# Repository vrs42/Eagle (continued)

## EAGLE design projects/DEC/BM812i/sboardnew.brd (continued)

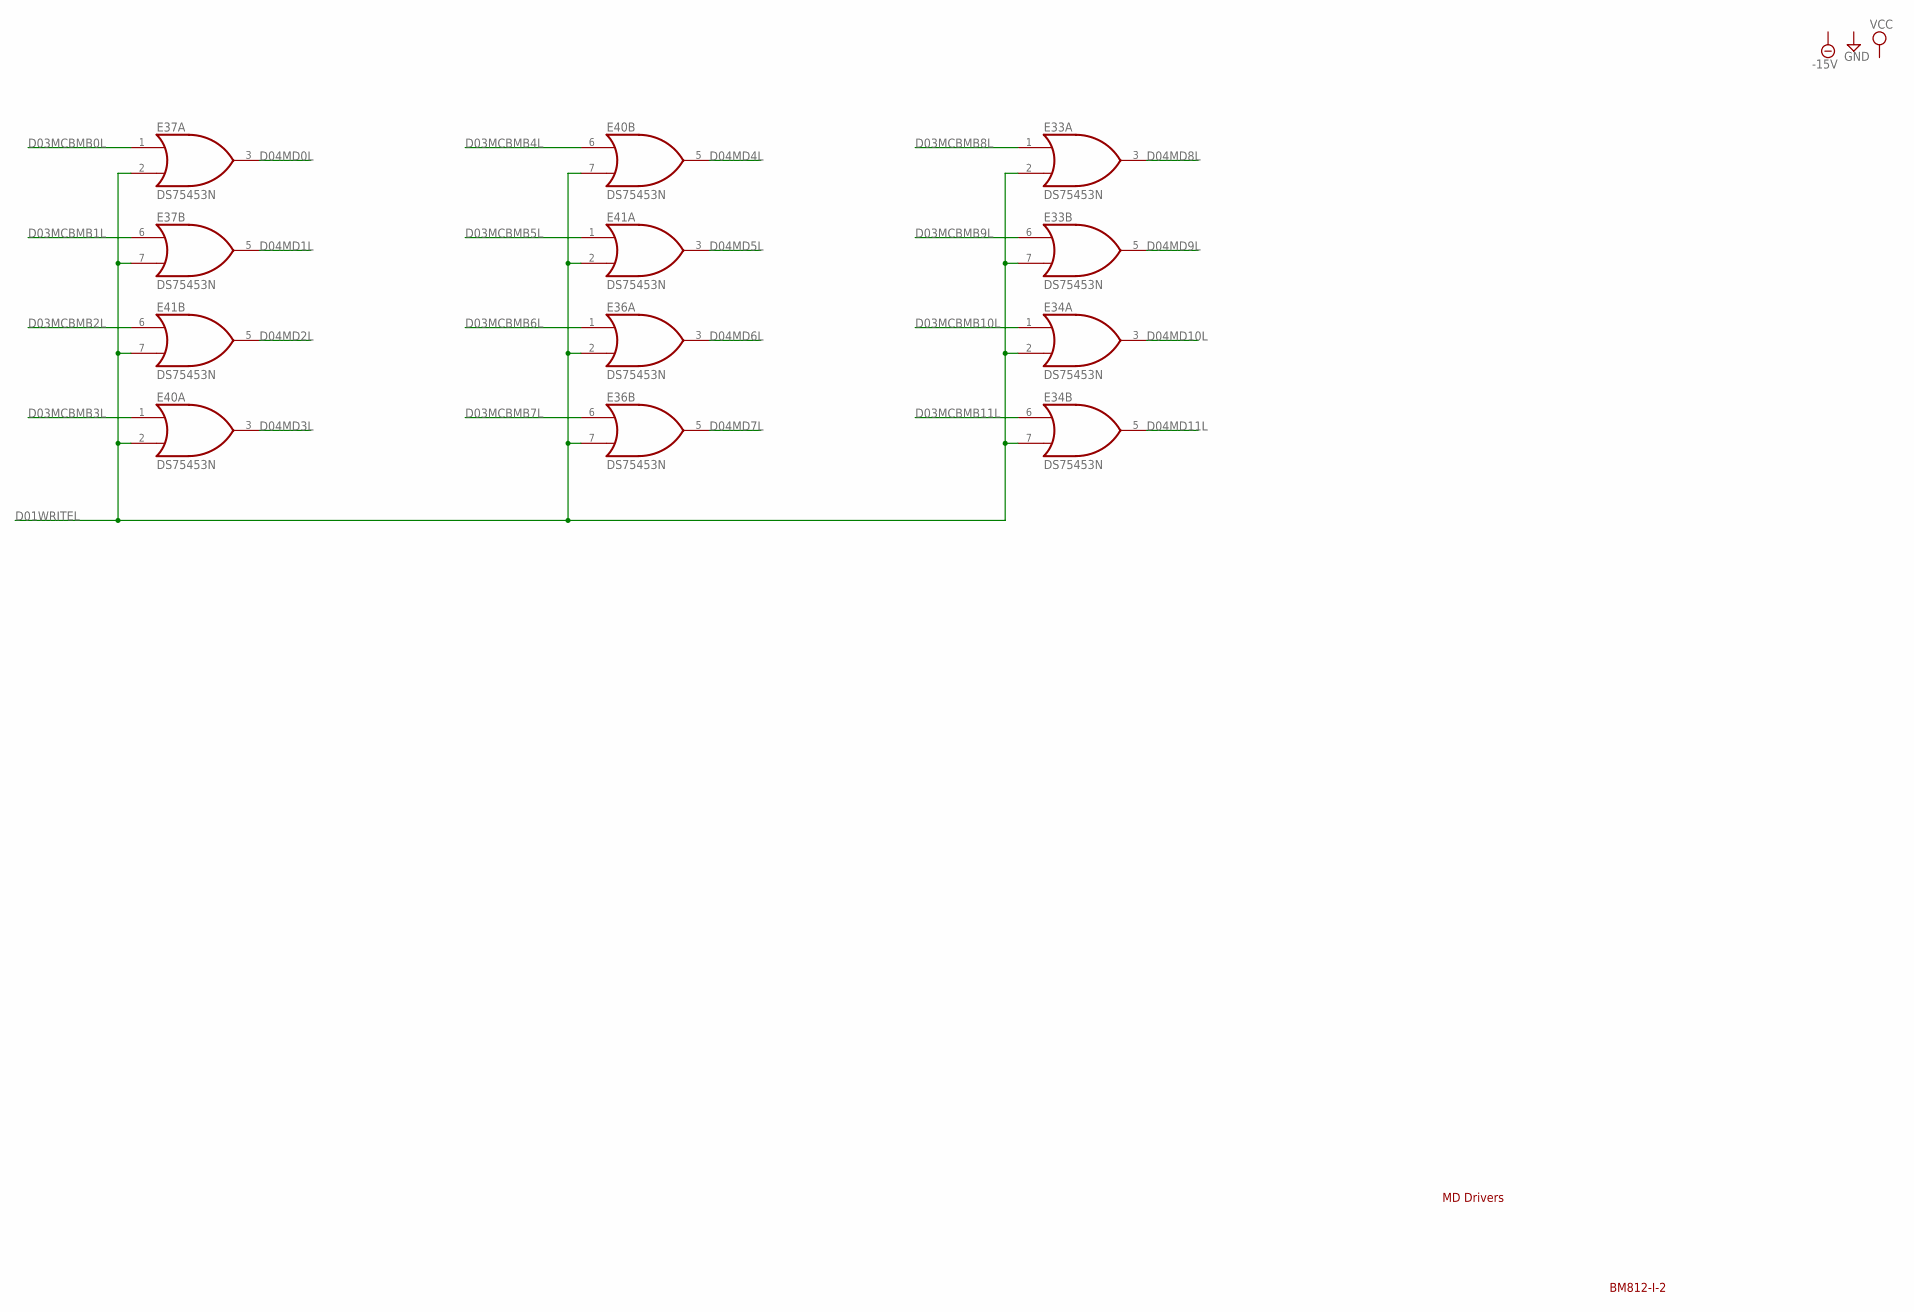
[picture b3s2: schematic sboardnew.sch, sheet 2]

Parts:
E33, E34, E36, E37, E40, E41: DS75453N; DIL08

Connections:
D01WRITEL: E33.2 (I1), E33.7 (I1), E34.2 (I1), E34.7 (I1), E36.2 (I1), E36.7 (I1), E37.2 (I1), E37.7 (I1), E40.2 (I1), E40.7 (I1), E41.2 (I1), E41.7 (I1); also elsewhere on the board
D03MCBMB0L: E37.1 (I0); also elsewhere on the board
D03MCBMB1L: E37.6 (I0); also elsewhere on the board
D03MCBMB2L: E41.6 (I0); also elsewhere on the board
D03MCBMB3L: E40.1 (I0); also elsewhere on the board
D03MCBMB4L: E40.6 (I0); also elsewhere on the board
D03MCBMB5L: E41.1 (I0); also elsewhere on the board
D03MCBMB6L: E36.1 (I0); also elsewhere on the board
D03MCBMB7L: E36.6 (I0); also elsewhere on the board
D03MCBMB8L: E33.1 (I0); also elsewhere on the board
D03MCBMB9L: E33.6 (I0); also elsewhere on the board
D03MCBMB10L: E34.1 (I0); also elsewhere on the board
D03MCBMB11L: E34.6 (I0); also elsewhere on the board
D04MD0L: E37.3 (O); also elsewhere on the board
D04MD1L: E37.5 (O); also elsewhere on the board
D04MD2L: E41.5 (O); also elsewhere on the board
D04MD3L: E40.3 (O); also elsewhere on the board
D04MD4L: E40.5 (O); also elsewhere on the board
D04MD5L: E41.3 (O); also elsewhere on the board
D04MD6L: E36.3 (O); also elsewhere on the board
D04MD7L: E36.5 (O); also elsewhere on the board
D04MD8L: E33.3 (O); also elsewhere on the board
D04MD9L: E33.5 (O); also elsewhere on the board
D04MD10L: E34.3 (O); also elsewhere on the board
D04MD11L: E34.5 (O); also elsewhere on the board
GND: E33.4 (GND), E34.4 (GND), E36.4 (GND), E37.4 (GND), E40.4 (GND), E41.4 (GND); also elsewhere on the board
VCC: E33.8 (VCC), E34.8 (VCC), E36.8 (VCC), E37.8 (VCC), E40.8 (VCC), E41.8 (VCC); also elsewhere on the board

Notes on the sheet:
BM812-I-2
MD Drivers

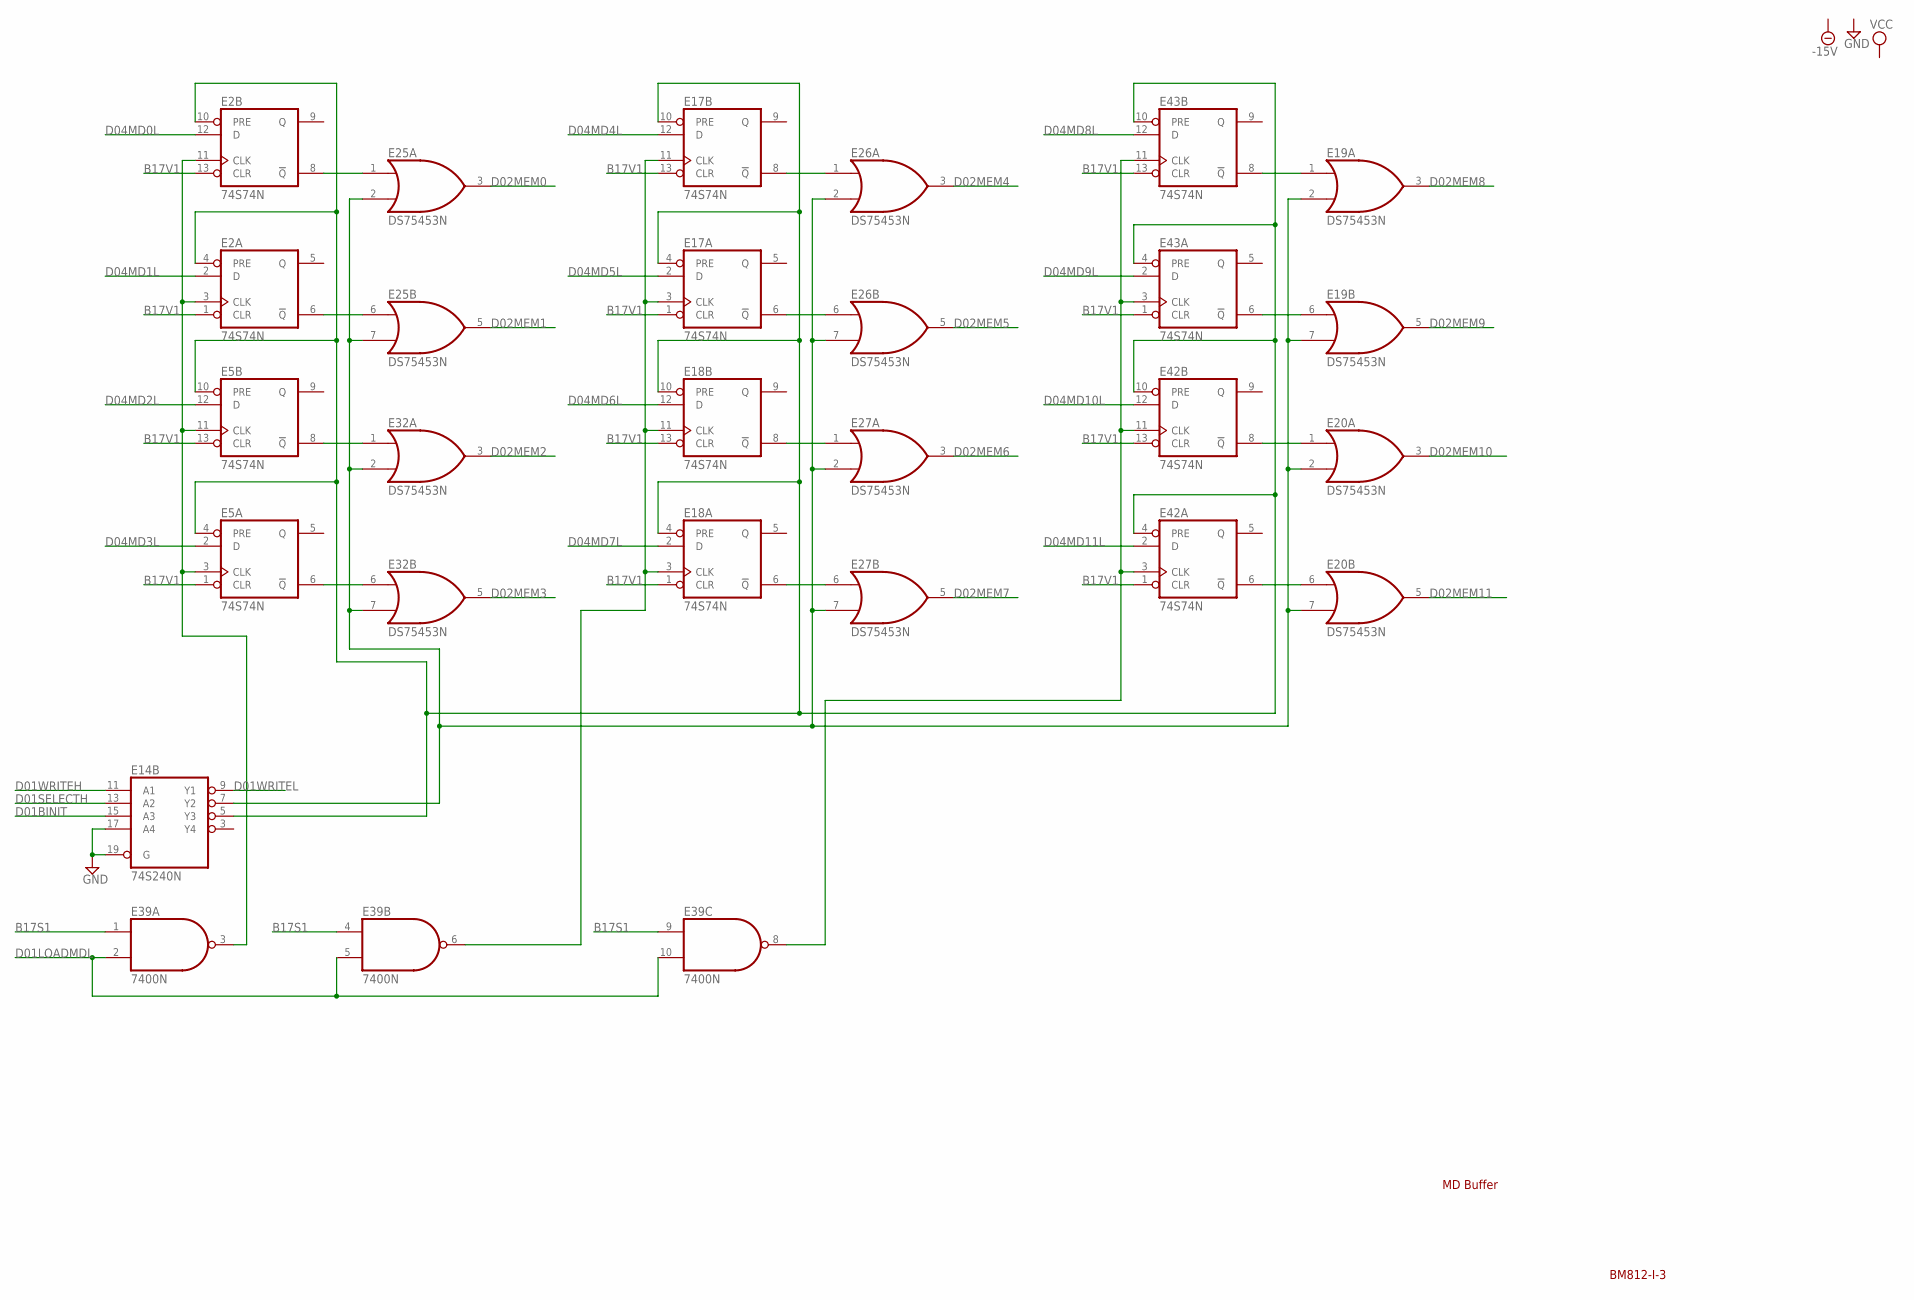
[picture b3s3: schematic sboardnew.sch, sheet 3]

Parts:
E2, E5, E17, E18, E42, E43: 74S74N; DIL14
E14: 74S240N; DIL20
E19, E20, E25, E26, E27, E32: DS75453N; DIL08
E39: 7400N; DIL14

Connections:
B17S1: E39.1 (I0), E39.4 (I0), E39.9 (I0); also elsewhere on the board
B17V1: E2.1 (CLR), E2.13 (CLR), E5.1 (CLR), E5.13 (CLR), E17.1 (CLR), E17.13 (CLR), E18.1 (CLR), E18.13 (CLR), E42.1 (CLR), E42.13 (CLR), E43.1 (CLR), E43.13 (CLR); also elsewhere on the board
D01BINIT: E14.15 (A3); also elsewhere on the board
D01LOADMDL: E39.2 (I1), E39.5 (I1), E39.10 (I1); also elsewhere on the board
D01SELECTH: E14.13 (A2); also elsewhere on the board
D01WRITEH: E14.11 (A1); also elsewhere on the board
D01WRITEL: E14.9 (Y1); also elsewhere on the board
D02MEM0: E25.3 (O); also elsewhere on the board
D02MEM1: E25.5 (O); also elsewhere on the board
D02MEM2: E32.3 (O); also elsewhere on the board
D02MEM3: E32.5 (O); also elsewhere on the board
D02MEM4: E26.3 (O); also elsewhere on the board
D02MEM5: E26.5 (O); also elsewhere on the board
D02MEM6: E27.3 (O); also elsewhere on the board
D02MEM7: E27.5 (O); also elsewhere on the board
D02MEM8: E19.3 (O); also elsewhere on the board
D02MEM9: E19.5 (O); also elsewhere on the board
D02MEM10: E20.3 (O); also elsewhere on the board
D02MEM11: E20.5 (O); also elsewhere on the board
D04MD0L: E2.12 (D); also elsewhere on the board
D04MD1L: E2.2 (D); also elsewhere on the board
D04MD2L: E5.12 (D); also elsewhere on the board
D04MD3L: E5.2 (D); also elsewhere on the board
D04MD4L: E17.12 (D); also elsewhere on the board
D04MD5L: E17.2 (D); also elsewhere on the board
D04MD6L: E18.12 (D); also elsewhere on the board
D04MD7L: E18.2 (D); also elsewhere on the board
D04MD8L: E43.12 (D); also elsewhere on the board
D04MD9L: E43.2 (D); also elsewhere on the board
D04MD10L: E42.12 (D); also elsewhere on the board
D04MD11L: E42.2 (D); also elsewhere on the board
GND: E2.7 (GND), E5.7 (GND), E14.10 (GND), E14.17 (A4), E14.19 (G), E17.7 (GND), E18.7 (GND), E19.4 (GND), E20.4 (GND), E25.4 (GND), E26.4 (GND), E27.4 (GND), E32.4 (GND), E39.7 (GND), E42.7 (GND), E43.7 (GND); also elsewhere on the board
unnamed: E2.3 (CLK), E2.11 (CLK), E5.3 (CLK), E5.11 (CLK), E39.3 (O)
unnamed: E5.6 (!Q), E32.6 (I0)
unnamed: E2.8 (!Q), E25.1 (I0)
unnamed: E2.6 (!Q), E25.6 (I0)
unnamed: E17.3 (CLK), E17.11 (CLK), E18.3 (CLK), E18.11 (CLK), E39.6 (O)
unnamed: E5.8 (!Q), E32.1 (I0)
unnamed: E2.4 (PRE), E2.10 (PRE), E5.4 (PRE), E5.10 (PRE), E14.5 (Y3), E17.4 (PRE), E17.10 (PRE), E18.4 (PRE), E18.10 (PRE), E42.4 (PRE), E42.10 (PRE), E43.4 (PRE), E43.10 (PRE)
unnamed: E14.7 (Y2), E19.2 (I1), E19.7 (I1), E20.2 (I1), E20.7 (I1), E25.2 (I1), E25.7 (I1), E26.2 (I1), E26.7 (I1), E27.2 (I1), E27.7 (I1), E32.2 (I1), E32.7 (I1)
unnamed: E17.6 (!Q), E26.6 (I0)
unnamed: E18.6 (!Q), E27.6 (I0)
unnamed: E18.8 (!Q), E27.1 (I0)
unnamed: E17.8 (!Q), E26.1 (I0)
unnamed: E20.6 (I0), E42.6 (!Q)
unnamed: E20.1 (I0), E42.8 (!Q)
unnamed: E39.8 (O), E42.3 (CLK), E42.11 (CLK), E43.3 (CLK), E43.11 (CLK)
unnamed: E19.6 (I0), E43.6 (!Q)
unnamed: E19.1 (I0), E43.8 (!Q)
VCC: E2.14 (VCC), E5.14 (VCC), E14.20 (VCC), E17.14 (VCC), E18.14 (VCC), E19.8 (VCC), E20.8 (VCC), E25.8 (VCC), E26.8 (VCC), E27.8 (VCC), E32.8 (VCC), E39.14 (VCC), E42.14 (VCC), E43.14 (VCC); also elsewhere on the board

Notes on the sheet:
MD Buffer
BM812-I-3

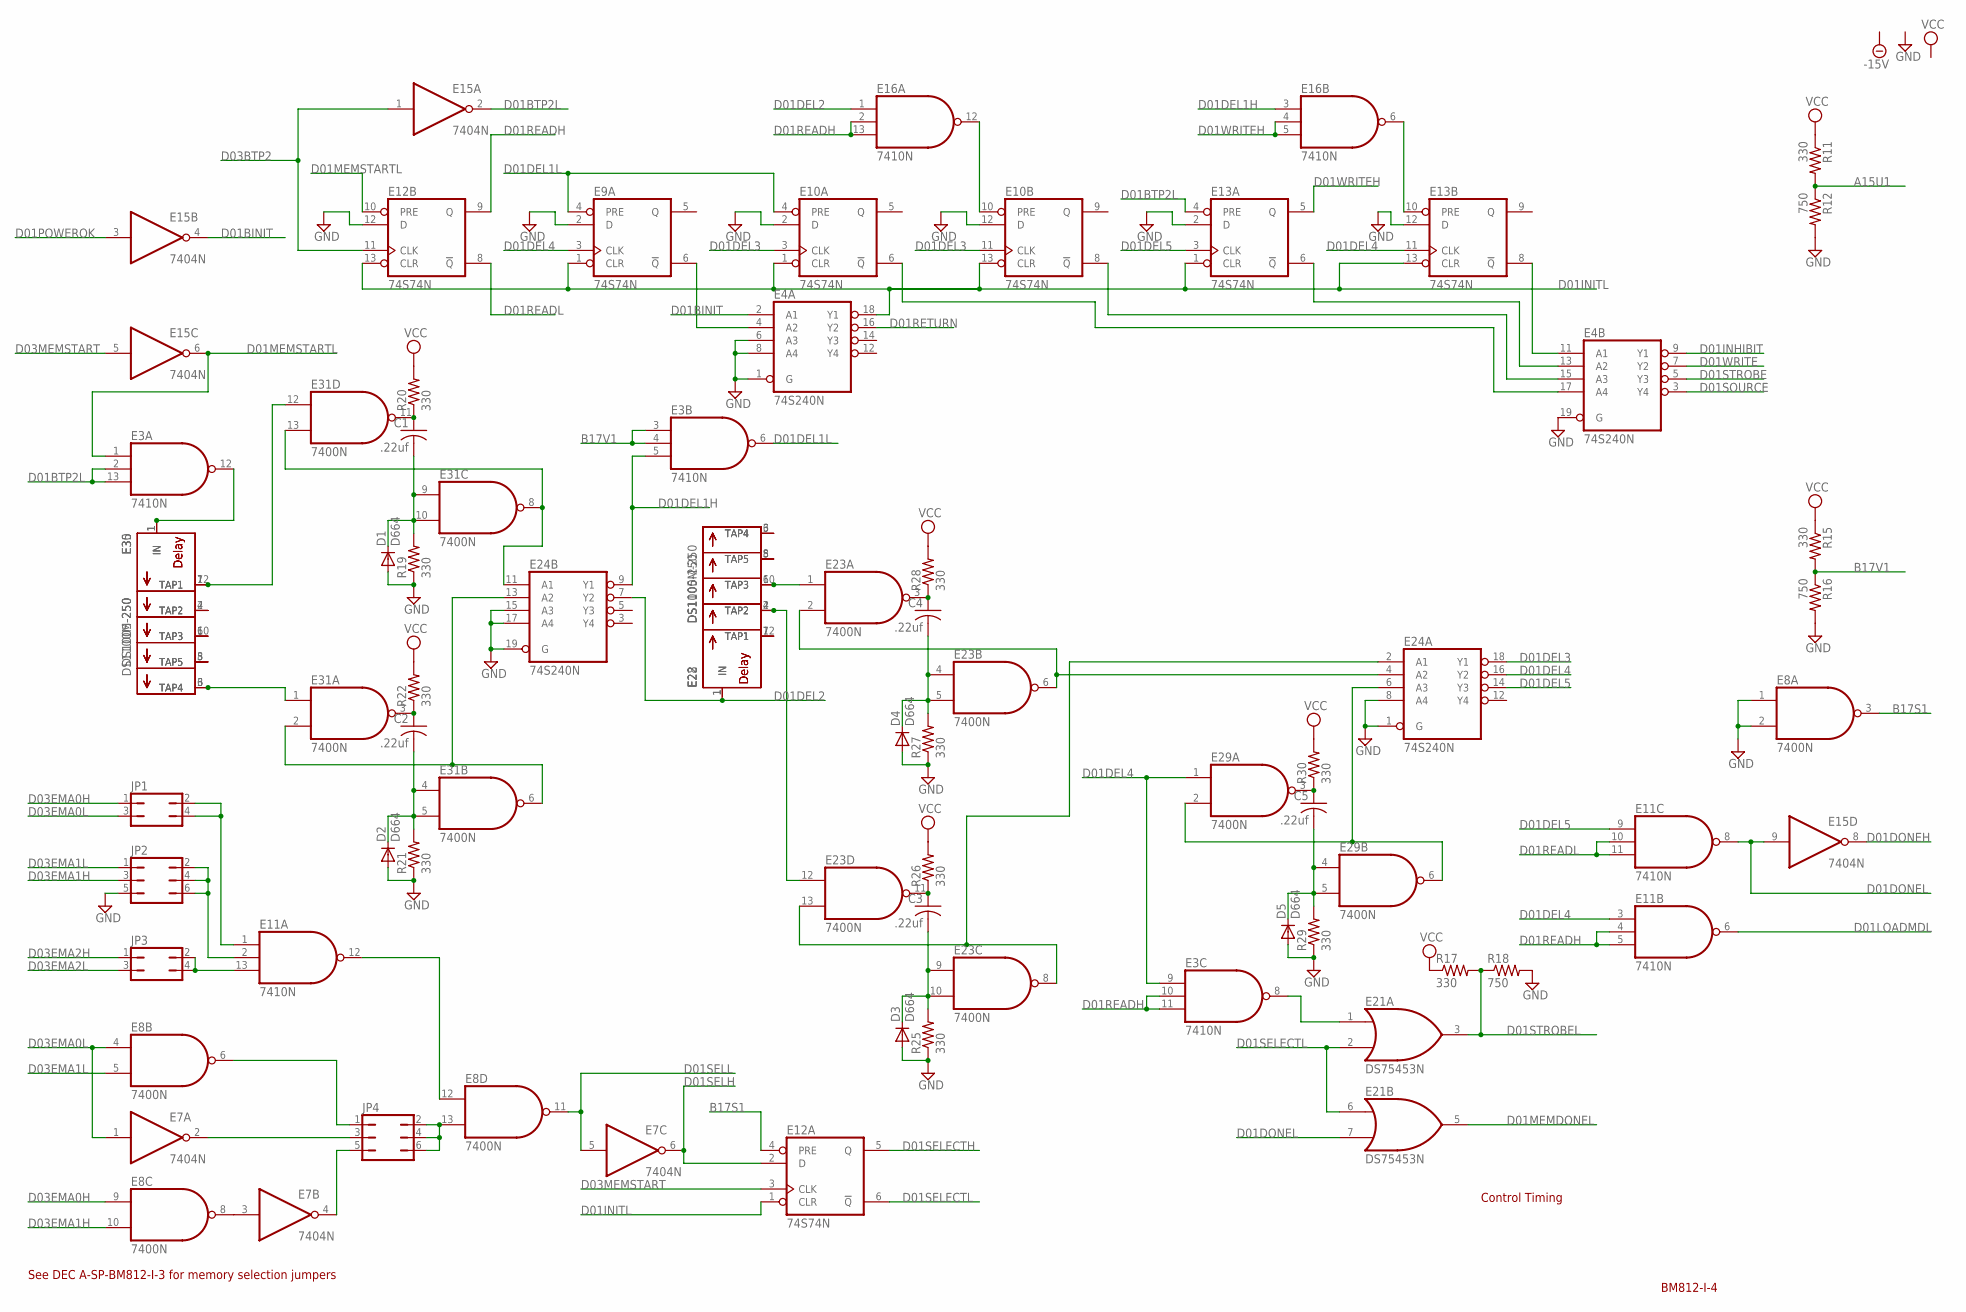
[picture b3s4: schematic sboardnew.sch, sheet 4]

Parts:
C1, C2, C3, C4, C5: .22uf; C050-025X075
D1, D2, D3, D4, D5: D664; DO35-10
E3, E11, E16: 7410N; DIL14
E4, E24: 74S240N; DIL20
E7, E15: 7404N; DIL14
E8, E23, E29, E31: 7400N; DIL14
E9, E10, E12, E13: 74S74N; DIL14
E21: DS75453N; DIL08
E22, E35: DS1100M-250; DIL08
E28, E30: DS1005-250; DIL14
JP1, JP3: JP2Q
JP2, JP4: JP3Q
R11, R15, R17, R19, R20, R21, R22, R25, R26, R27, R28, R29, R30: 330; 0207/10
R12, R16, R18: 750; 0207/10

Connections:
A15U1: R11.2, R12.1; also elsewhere on the board
B17S1: E8.3 (O), E12.4 (PRE); also elsewhere on the board
B17V1: E3.3 (I0), E3.4 (I1), R15.2, R16.1; also elsewhere on the board
D01BINIT: E4.2 (A1), E15.4 (O); also elsewhere on the board
D01BTP2L: E3.2 (I1), E3.13 (I2), E13.4 (PRE), E15.2 (O)
D01DEL1H: E3.5 (I2), E16.3 (I0), E24.9 (Y1)
D01DEL1L: E3.6 (O), E9.4 (PRE), E10.4 (PRE)
D01DEL2: E16.1 (I0), E22.1 (IN), E24.7 (Y2), E28.1 (IN)
D01DEL3: E10.3 (CLK), E10.11 (CLK), E24.18 (Y1)
D01DEL4: E3.9 (I0), E9.3 (CLK), E11.3 (I0), E13.11 (CLK), E24.16 (Y2), E29.1 (I0)
D01DEL5: E11.9 (I0), E13.3 (CLK), E24.14 (Y3)
D01DONEH: E15.8 (O); also elsewhere on the board
D01DONEL: E11.8 (O), E15.9 (I), E21.7 (I1)
D01INHIBIT: E4.9 (Y1); also elsewhere on the board
D01INITL: E4.18 (Y1), E9.1 (CLR), E10.1 (CLR), E10.13 (CLR), E12.1 (CLR), E12.13 (CLR), E13.1 (CLR), E13.13 (CLR)
D01LOADMDL: E11.6 (O); also elsewhere on the board
D01MEMDONEL: E21.5 (O); also elsewhere on the board
D01MEMSTARTL: E3.1 (I0), E12.10 (PRE), E15.6 (O)
D01POWEROK: E15.3 (I); also elsewhere on the board
D01READH: E3.10 (I1), E3.11 (I2), E11.4 (I1), E11.5 (I2), E12.9 (Q), E16.2 (I1), E16.13 (I2)
D01READL: E11.10 (I1), E11.11 (I2), E12.8 (!Q); also elsewhere on the board
D01RETURN: E4.16 (Y2); also elsewhere on the board
D01SELECTH: E12.5 (Q); also elsewhere on the board
D01SELECTL: E12.6 (!Q), E21.2 (I1), E21.6 (I0)
D01SELH: E7.6 (O), E12.2 (D)
D01SELL: E7.5 (I), E8.11 (O)
D01SOURCE: E4.3 (Y4); also elsewhere on the board
D01STROBE: E4.5 (Y3); also elsewhere on the board
D01STROBEL: E21.3 (O), R17.2, R18.1; also elsewhere on the board
D01WRITE: E4.7 (Y2); also elsewhere on the board
D01WRITEH: E13.5 (Q), E16.4 (I1), E16.5 (I2); also elsewhere on the board
D03BTP2: E12.11 (CLK), E15.1 (I); also elsewhere on the board
D03EMA0H: E8.9 (I0), JP1.1; also elsewhere on the board
D03EMA0L: E7.1 (I), E8.4 (I0), JP1.3; also elsewhere on the board
D03EMA1H: E8.10 (I1), JP2.3; also elsewhere on the board
D03EMA1L: E8.5 (I1), JP2.1; also elsewhere on the board
D03EMA2H: JP3.1; also elsewhere on the board
D03EMA2L: JP3.3; also elsewhere on the board
D03MEMSTART: E12.3 (CLK), E15.5 (I); also elsewhere on the board
GND: D1.A, D2.A, D3.A, D4.A, D5.A, E3.7 (GND), E4.1 (G), E4.6 (A3), E4.8 (A4), E4.10 (GND), E4.19 (G), E7.7 (GND), E8.1 (I0), E8.2 (I1), E8.7 (GND), E9.2 (D), E9.7 (GND), E10.2 (D), E10.7 (GND), E10.12 (D), E11.7 (GND), E12.7 (GND), E12.12 (D), E13.2 (D), E13.7 (GND), E13.12 (D), E15.7 (GND), E16.7 (GND), E21.4 (GND), E22.4 (GND), E23.7 (GND), E24.1 (G), E24.8 (A4), E24.10 (GND), E24.15 (A3), E24.17 (A4), E24.19 (G), E28.7 (GND), E29.7 (GND), E30.7 (GND), E31.7 (GND), E35.4 (GND), JP2.5, R12.2, R16.2, R18.2, R19.1, R21.1, R25.1, R27.1, R29.1; also elsewhere on the board
unnamed: C3.2, D3.C, E23.9 (I0), E23.10 (I1), R25.2
unnamed: C5.2, D5.C, E29.4 (I0), E29.5 (I1), R29.2
unnamed: E8.13 (I1), JP4.2, JP4.4, JP4.6
unnamed: C2.2, D2.C, E31.4 (I0), E31.5 (I1), R21.2
unnamed: E30.12 (TAP1), E31.12 (I0), E35.7 (TAP1)
unnamed: E22.2 (TAP2), E23.12 (I0), E28.4 (TAP2)
unnamed: C1.2, D1.C, E31.9 (I0), E31.10 (I1), R19.2
unnamed: E24.11 (A1), E31.8 (O), E31.13 (I1)
unnamed: C1.1, E31.11 (O), R20.1
unnamed: C2.1, E31.3 (O), R22.1
unnamed: E24.13 (A2), E31.2 (I1), E31.6 (O)
unnamed: C3.1, E23.11 (O), R26.1
unnamed: E30.6 (TAP4), E31.1 (I0), E35.3 (TAP4)
unnamed: E23.8 (O), E23.13 (I1), E24.2 (A1)
unnamed: C4.2, D4.C, E23.4 (I0), E23.5 (I1), R27.2
unnamed: C4.1, E23.3 (O), R28.1
unnamed: E3.12 (O), E30.1 (IN), E35.1 (IN)
unnamed: E23.2 (I1), E23.6 (O), E24.4 (A2)
unnamed: E22.6 (TAP3), E23.1 (I0), E28.10 (TAP3)
unnamed: C5.1, E29.3 (O), R30.1
unnamed: E24.6 (A3), E29.2 (I1), E29.6 (O)
unnamed: E10.10 (PRE), E16.12 (O)
unnamed: E22.7 (TAP1), E28.12 (TAP1)
unnamed: E22.3 (TAP4), E28.6 (TAP4)
unnamed: E22.5 (TAP5), E28.8 (TAP5)
unnamed: E30.4 (TAP2), E35.2 (TAP2)
unnamed: E30.10 (TAP3), E35.6 (TAP3)
unnamed: E30.8 (TAP5), E35.5 (TAP5)
unnamed: E8.6 (O), JP4.1
unnamed: E13.10 (PRE), E16.6 (O)
unnamed: E3.8 (O), E21.1 (I0)
unnamed: E4.4 (A2), E9.6 (!Q)
unnamed: E4.17 (A4), E10.6 (!Q)
unnamed: E4.15 (A3), E10.8 (!Q)
unnamed: E7.2 (O), JP4.3
unnamed: E4.13 (A2), E13.6 (!Q)
unnamed: E7.3 (I), E8.8 (O)
unnamed: E4.11 (A1), E13.8 (!Q)
unnamed: E7.4 (O), JP4.5
unnamed: E11.13 (I2), JP3.2, JP3.4
unnamed: E11.2 (I1), JP2.2, JP2.4, JP2.6
unnamed: E11.1 (I0), JP1.2, JP1.4
unnamed: E8.12 (I0), E11.12 (O)
VCC: E3.14 (VCC), E4.20 (VCC), E7.14 (VCC), E8.14 (VCC), E9.14 (VCC), E10.14 (VCC), E11.14 (VCC), E12.14 (VCC), E13.14 (VCC), E15.14 (VCC), E16.14 (VCC), E21.8 (VCC), E22.8 (VCC), E23.14 (VCC), E24.20 (VCC), E28.14 (VCC), E29.14 (VCC), E30.14 (VCC), E31.14 (VCC), E35.8 (VCC), R11.1, R15.1, R17.1, R20.2, R22.2, R26.2, R28.2, R30.2; also elsewhere on the board

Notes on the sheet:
BM812-I-4
Control Timing
See DEC A-SP-BM812-I-3 for memory selection jumpers

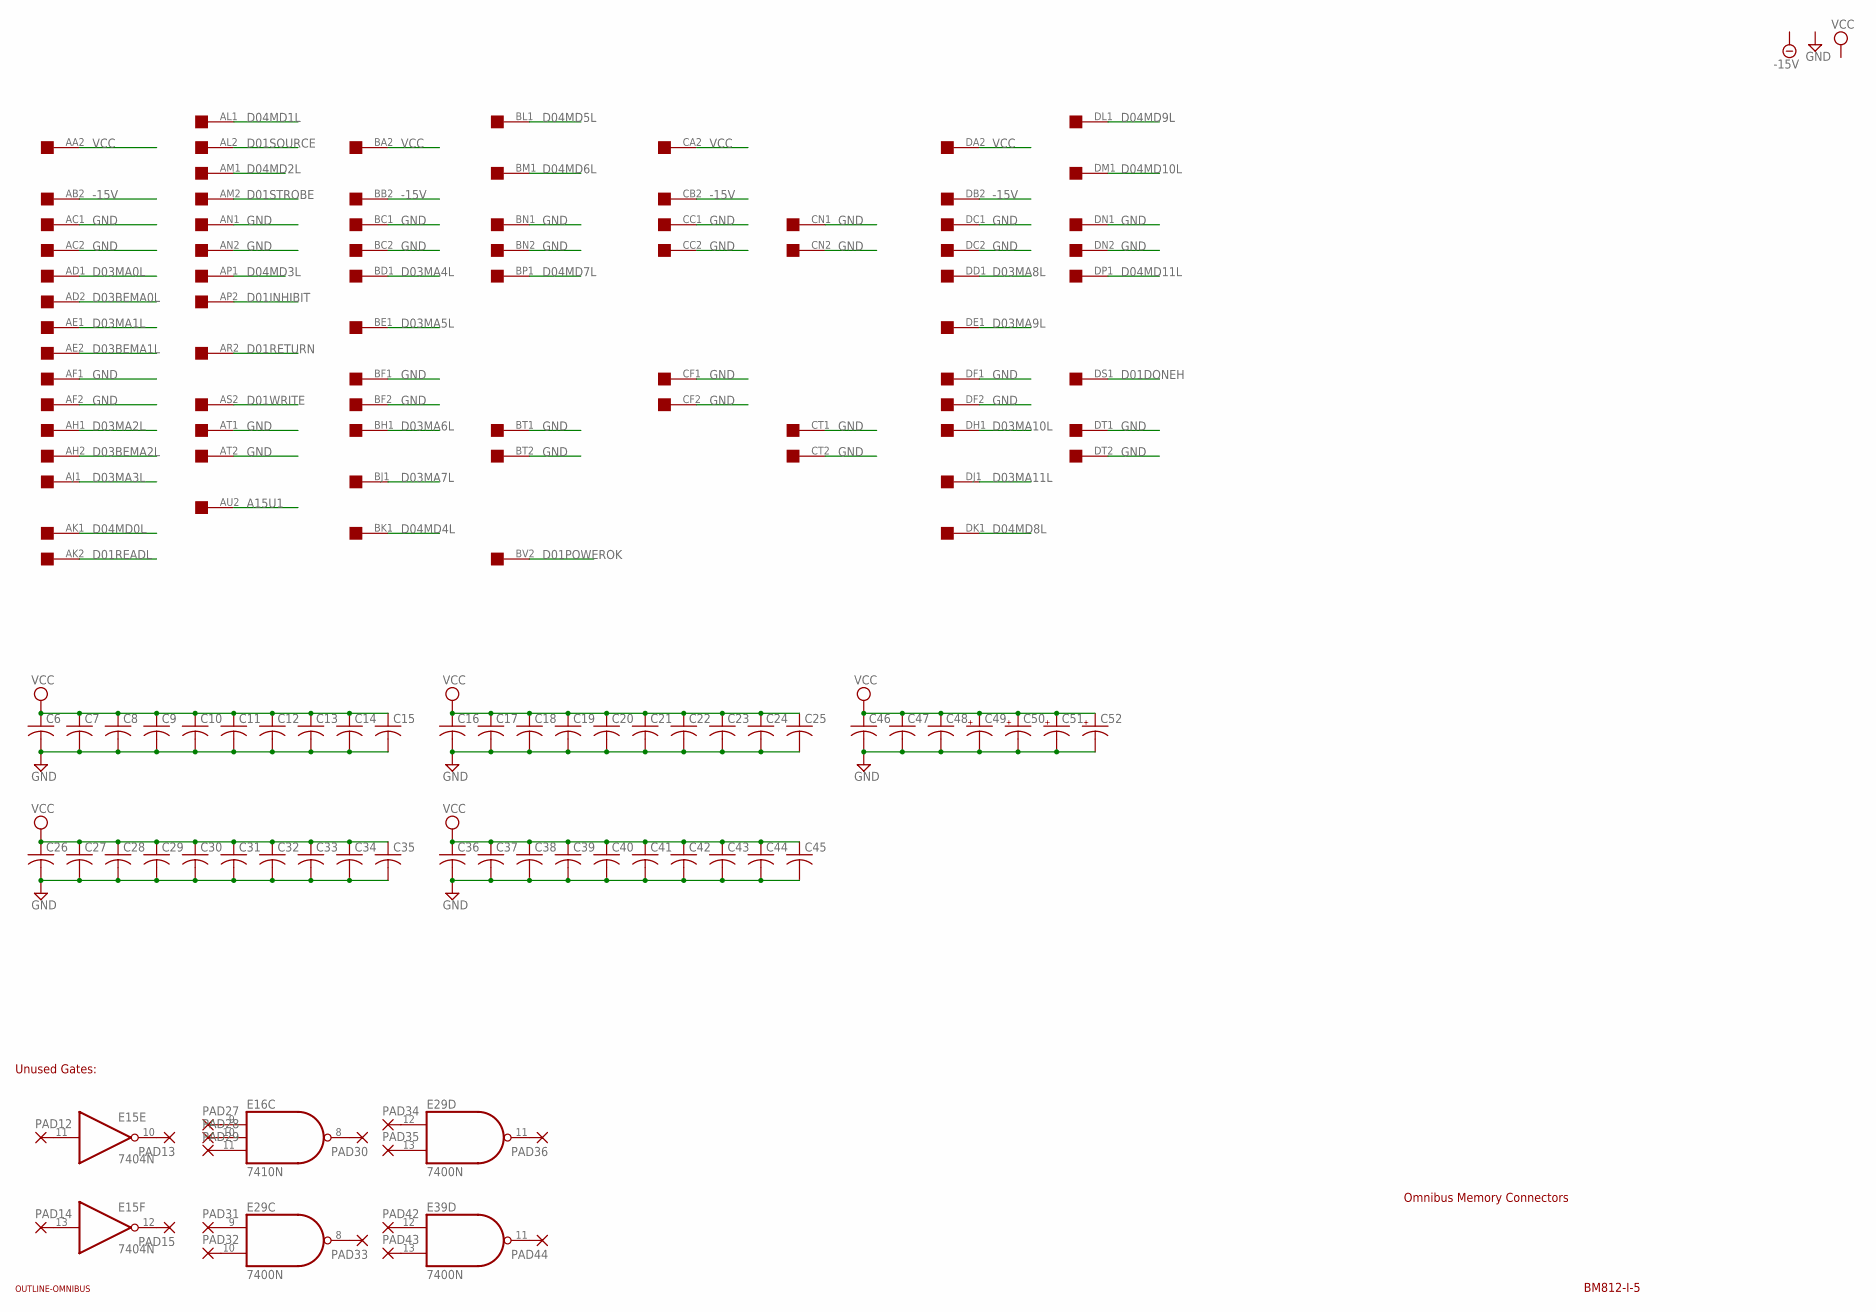
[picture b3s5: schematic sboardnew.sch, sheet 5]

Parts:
C6, C7, C8, C9, C10, C11, C12, C13, C14, C15, C16, C17, C18, C19, C20, C21, C22, C23, C24, C25, C26, C27, C28, C29, C30, C31, C32, C33, C34, C35, C36, C37, C38, C39, C40, C41, C42, C43, C44, C45, C46, C47, C48: C-US050-025X075; C050-025X075
C49, C50, C51, C52: CPOL-USE22-6AXIAL; E22-6
E15: 7404N; DIL14
E16: 7410N; DIL14
E29, E39: 7400N; DIL14
PAD12, PAD13, PAD14, PAD15, PAD27, PAD28, PAD29, PAD30, PAD31, PAD32, PAD33, PAD34, PAD35, PAD36, PAD42, PAD43, PAD44: 1,6/0,8
U$1: QUAD; EDGE-CON8
U$2: OUTLINE-OMNIBUS; OMNIBUS

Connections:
-15V: U$1.AB2, U$1.BB2, U$1.CB2, U$1.DB2
A15U1: U$1.AU2; also elsewhere on the board
D01DONEH: U$1.DS1; also elsewhere on the board
D01INHIBIT: U$1.AP2; also elsewhere on the board
D01POWEROK: U$1.BV2; also elsewhere on the board
D01READL: U$1.AK2; also elsewhere on the board
D01RETURN: U$1.AR2; also elsewhere on the board
D01SOURCE: U$1.AL2; also elsewhere on the board
D01STROBE: U$1.AM2; also elsewhere on the board
D01WRITE: U$1.AS2; also elsewhere on the board
D03BEMA0L: U$1.AD2; also elsewhere on the board
D03BEMA1L: U$1.AE2; also elsewhere on the board
D03BEMA2L: U$1.AH2; also elsewhere on the board
D03MA0L: U$1.AD1; also elsewhere on the board
D03MA1L: U$1.AE1; also elsewhere on the board
D03MA2L: U$1.AH1; also elsewhere on the board
D03MA3L: U$1.AJ1; also elsewhere on the board
D03MA4L: U$1.BD1; also elsewhere on the board
D03MA5L: U$1.BE1; also elsewhere on the board
D03MA6L: U$1.BH1; also elsewhere on the board
D03MA7L: U$1.BJ1; also elsewhere on the board
D03MA8L: U$1.DD1; also elsewhere on the board
D03MA9L: U$1.DE1; also elsewhere on the board
D03MA10L: U$1.DH1; also elsewhere on the board
D03MA11L: U$1.DJ1; also elsewhere on the board
D04MD0L: U$1.AK1; also elsewhere on the board
D04MD1L: U$1.AL1; also elsewhere on the board
D04MD2L: U$1.AM1; also elsewhere on the board
D04MD3L: U$1.AP1; also elsewhere on the board
D04MD4L: U$1.BK1; also elsewhere on the board
D04MD5L: U$1.BL1; also elsewhere on the board
D04MD6L: U$1.BM1; also elsewhere on the board
D04MD7L: U$1.BP1; also elsewhere on the board
D04MD8L: U$1.DK1; also elsewhere on the board
D04MD9L: U$1.DL1; also elsewhere on the board
D04MD10L: U$1.DM1; also elsewhere on the board
D04MD11L: U$1.DP1; also elsewhere on the board
GND: C6.2, C7.2, C8.2, C9.2, C10.2, C11.2, C12.2, C13.2, C14.2, C15.2, C16.2, C17.2, C18.2, C19.2, C20.2, C21.2, C22.2, C23.2, C24.2, C25.2, C26.2, C27.2, C28.2, C29.2, C30.2, C31.2, C32.2, C33.2, C34.2, C35.2, C36.2, C37.2, C38.2, C39.2, C40.2, C41.2, C42.2, C43.2, C44.2, C45.2, C46.2, C47.2, C48.2, C49.-, C50.-, C51.-, C52.-, E15.7 (GND), E16.7 (GND), E29.7 (GND), E39.7 (GND), U$1.AC1, U$1.AC2, U$1.AF1, U$1.AF2, U$1.AN1, U$1.AN2, U$1.AT1, U$1.AT2, U$1.BC1, U$1.BC2, U$1.BF1, U$1.BF2, U$1.BN1, U$1.BN2, U$1.BT1, U$1.BT2, U$1.CC1, U$1.CC2, U$1.CF1, U$1.CF2, U$1.CN1, U$1.CN2, U$1.CT1, U$1.CT2, U$1.DC1, U$1.DC2, U$1.DF1, U$1.DF2, U$1.DN1, U$1.DN2, U$1.DT1, U$1.DT2; also elsewhere on the board
unnamed: E15.11 (I), PAD12.1
unnamed: E15.10 (O), PAD13.1
unnamed: E15.13 (I), PAD14.1
unnamed: E15.12 (O), PAD15.1
unnamed: E16.9 (I0), PAD27.1
unnamed: E16.10 (I1), PAD28.1
unnamed: E16.11 (I2), PAD29.1
unnamed: E16.8 (O), PAD30.1
unnamed: E29.9 (I0), PAD31.1
unnamed: E29.10 (I1), PAD32.1
unnamed: E29.8 (O), PAD33.1
unnamed: E29.12 (I0), PAD34.1
unnamed: E29.13 (I1), PAD35.1
unnamed: E29.11 (O), PAD36.1
unnamed: E39.12 (I0), PAD42.1
unnamed: E39.13 (I1), PAD43.1
unnamed: E39.11 (O), PAD44.1
VCC: C6.1, C7.1, C8.1, C9.1, C10.1, C11.1, C12.1, C13.1, C14.1, C15.1, C16.1, C17.1, C18.1, C19.1, C20.1, C21.1, C22.1, C23.1, C24.1, C25.1, C26.1, C27.1, C28.1, C29.1, C30.1, C31.1, C32.1, C33.1, C34.1, C35.1, C36.1, C37.1, C38.1, C39.1, C40.1, C41.1, C42.1, C43.1, C44.1, C45.1, C46.1, C47.1, C48.1, C49.+, C50.+, C51.+, C52.+, E15.14 (VCC), E16.14 (VCC), E29.14 (VCC), E39.14 (VCC), U$1.AA2, U$1.BA2, U$1.CA2, U$1.DA2; also elsewhere on the board

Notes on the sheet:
Omnibus Memory Connectors
BM812-I-5
Unused Gates:

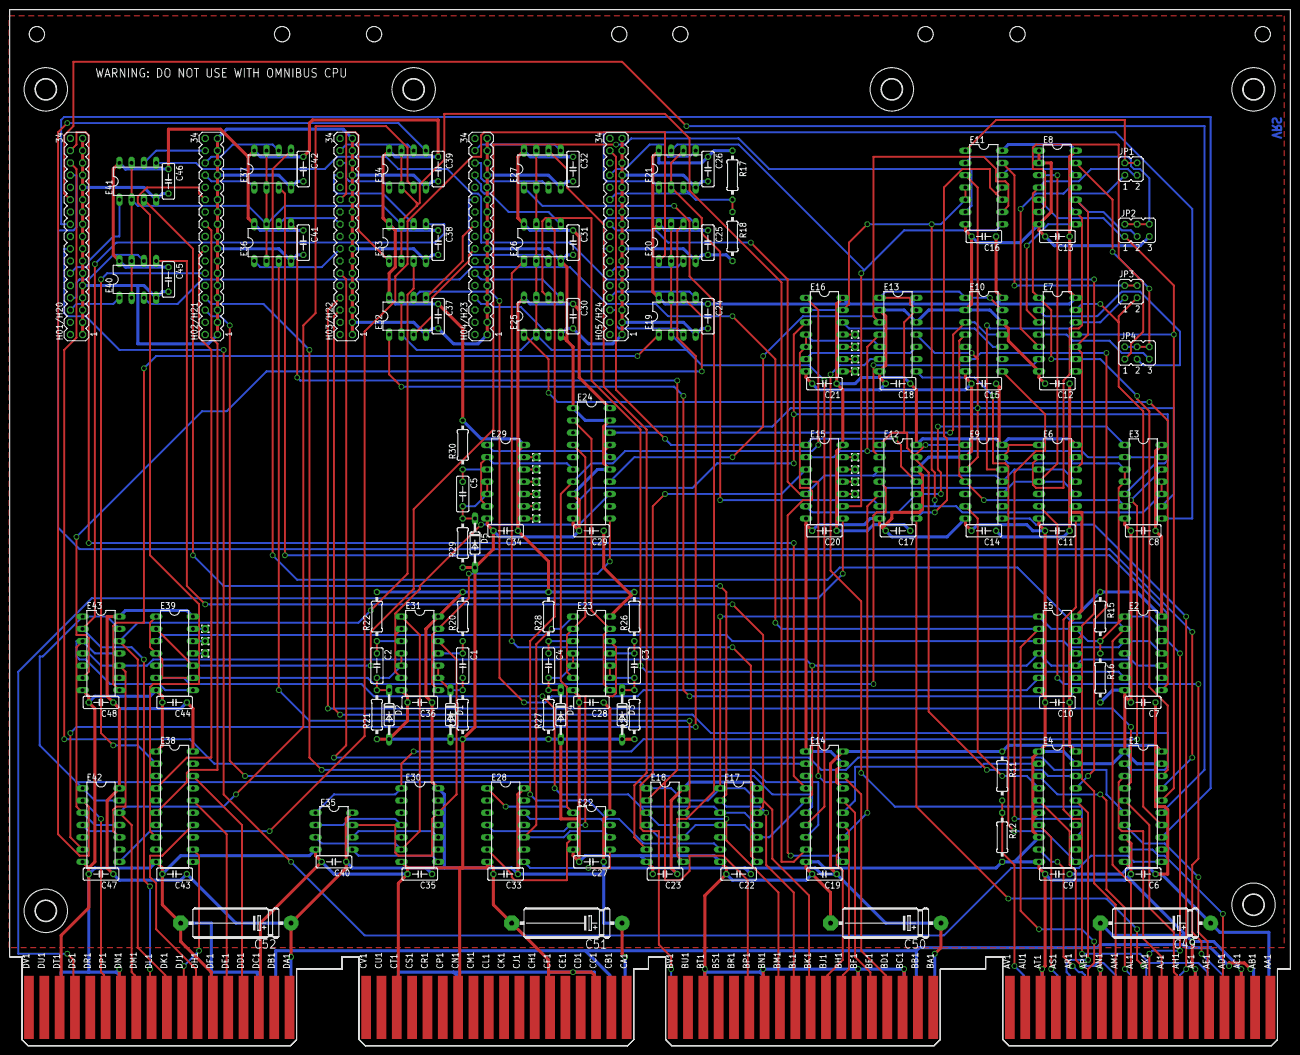
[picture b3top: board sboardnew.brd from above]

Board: 2 copper layers, 265.3 x 214.6 mm, 150 parts (0 on the bottom side), 186 nets.

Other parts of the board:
U$20, U$66, U$67, U$82, U$83, U$86: 4,3
